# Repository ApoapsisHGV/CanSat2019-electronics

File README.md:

# CanSat-Electronics
Circuit and PCB design files related to our 2019 CanSat competition

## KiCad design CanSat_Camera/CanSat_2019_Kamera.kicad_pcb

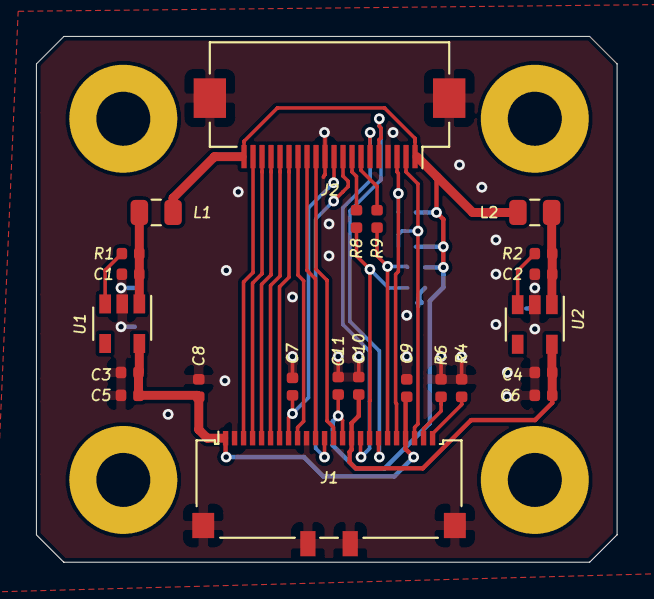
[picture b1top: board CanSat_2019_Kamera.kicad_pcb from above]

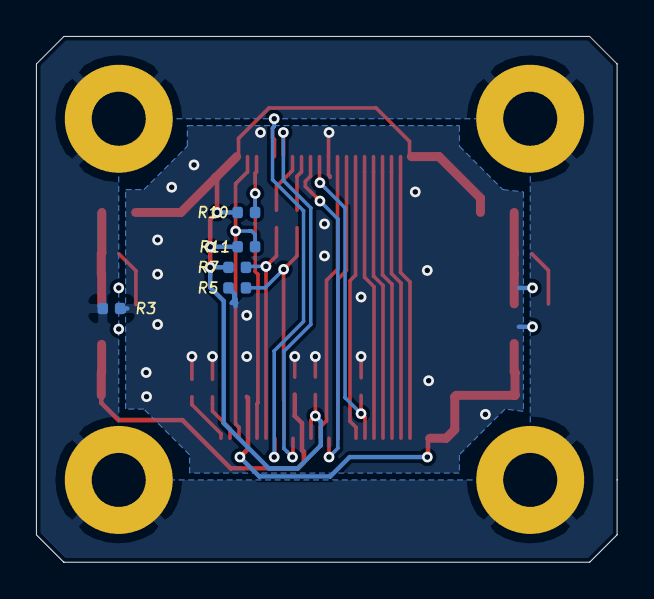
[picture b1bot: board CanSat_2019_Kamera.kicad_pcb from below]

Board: 2 copper layers, 32.3 x 29.2 mm, 32 parts (5 on the bottom side), 29 nets.

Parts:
C1, C2, C3, C4: 4.7u; C_0402_1005Metric
C5, C6, C8, C9, C10, C11: 100n; C_0402_1005Metric
C7: 15 pF; C_0402_1005Metric
H1, H2, H3, H4: MountingHole_Pad; MountingHole_3mm_Pad
J1: OV5640 24 Pin 0.5 mm; Molex_502244-2430_1x24-1MP_P0.5mm_Horizontal
J2: Camera Out 20 Pin 0.5 mm; Hirose_FH12-20S-0.5SH_1x20-1MP_P0.50mm_Horizontal
L1, L2: 3.3uH; L_0805_2012Metric
R1, R2, R4: 10k; R_0402_1005Metric
R3, R5, R6, R8, R9: 0; R_0402_1005Metric
R7, R10, R11: 4.7k; R_0402_1005Metric
U1: TLV75528PDBV; SOT-23-5
U2: TLV75518PDBV; SOT-23-5

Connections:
+1V8: C4.1, C6.1, C10.1, J1.15, U2.5
+2V8: C3.1, C5.1, C8.1, C9.1, J1.1, J1.21, U1.5
+3V3: C11.1, J1.14, J2.1, J2.20, L1.1, L2.1, R7.1, R10.1, R11.1
/D2: J1.6, J2.16
/D3: J1.4, J2.18
/D4: J1.3, J2.19
/D5: J1.5, J2.17
/D6: J1.7, J2.15
/D7: J1.9, J2.14
/D8: J1.11, J2.13
/D9: J1.13, J2.12
/H_REF: J1.16, J2.6
/P_CLK: C7.1, J1.8, J2.10
/P_DWN: J1.17, R5.1, R8.1
/RST: J1.19, R7.2, R9.1
/S_CLK: J1.20, J2.3, R10.2
/S_DAT: J1.22, J2.2, R11.2
/V_SYNC: J1.18, J2.5
/X_CLK: J1.12, J2.9
AGND: J1.23, R6.2
GND: C1.2, C2.2, C3.2, C4.2, C5.2, C6.2, C7.2, C8.2, C9.2, C10.2, C11.2, J1.2, J1.10, J1.MP, J2.4, J2.11, J2.MP, R3.2, R4.2, R5.2, R6.1, U1.2, U2.2
unnamed: C1.1, L1.2, R1.2, U1.1
unnamed: C2.1, L2.2, R2.2, U2.1
unnamed: H1.1, H2.1, H3.1, H4.1, R3.1
unnamed: J1.24, R4.1
unnamed: J2.7, R9.2
unnamed: J2.8, R8.2
unnamed: R1.1, U1.3
unnamed: R2.1, U2.3

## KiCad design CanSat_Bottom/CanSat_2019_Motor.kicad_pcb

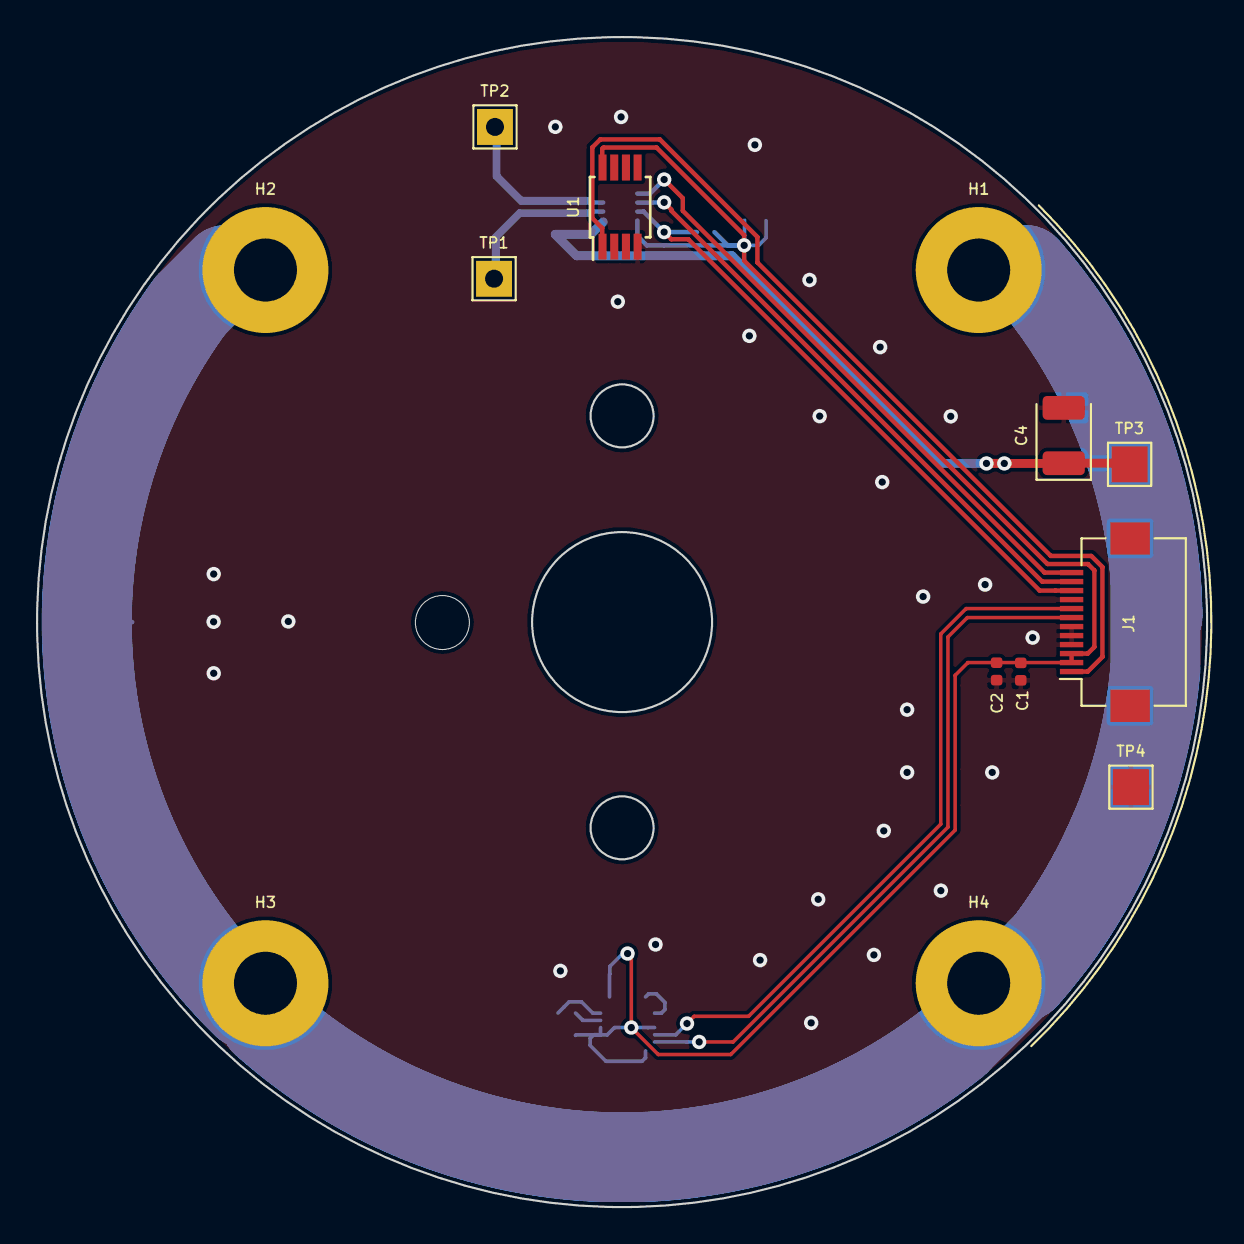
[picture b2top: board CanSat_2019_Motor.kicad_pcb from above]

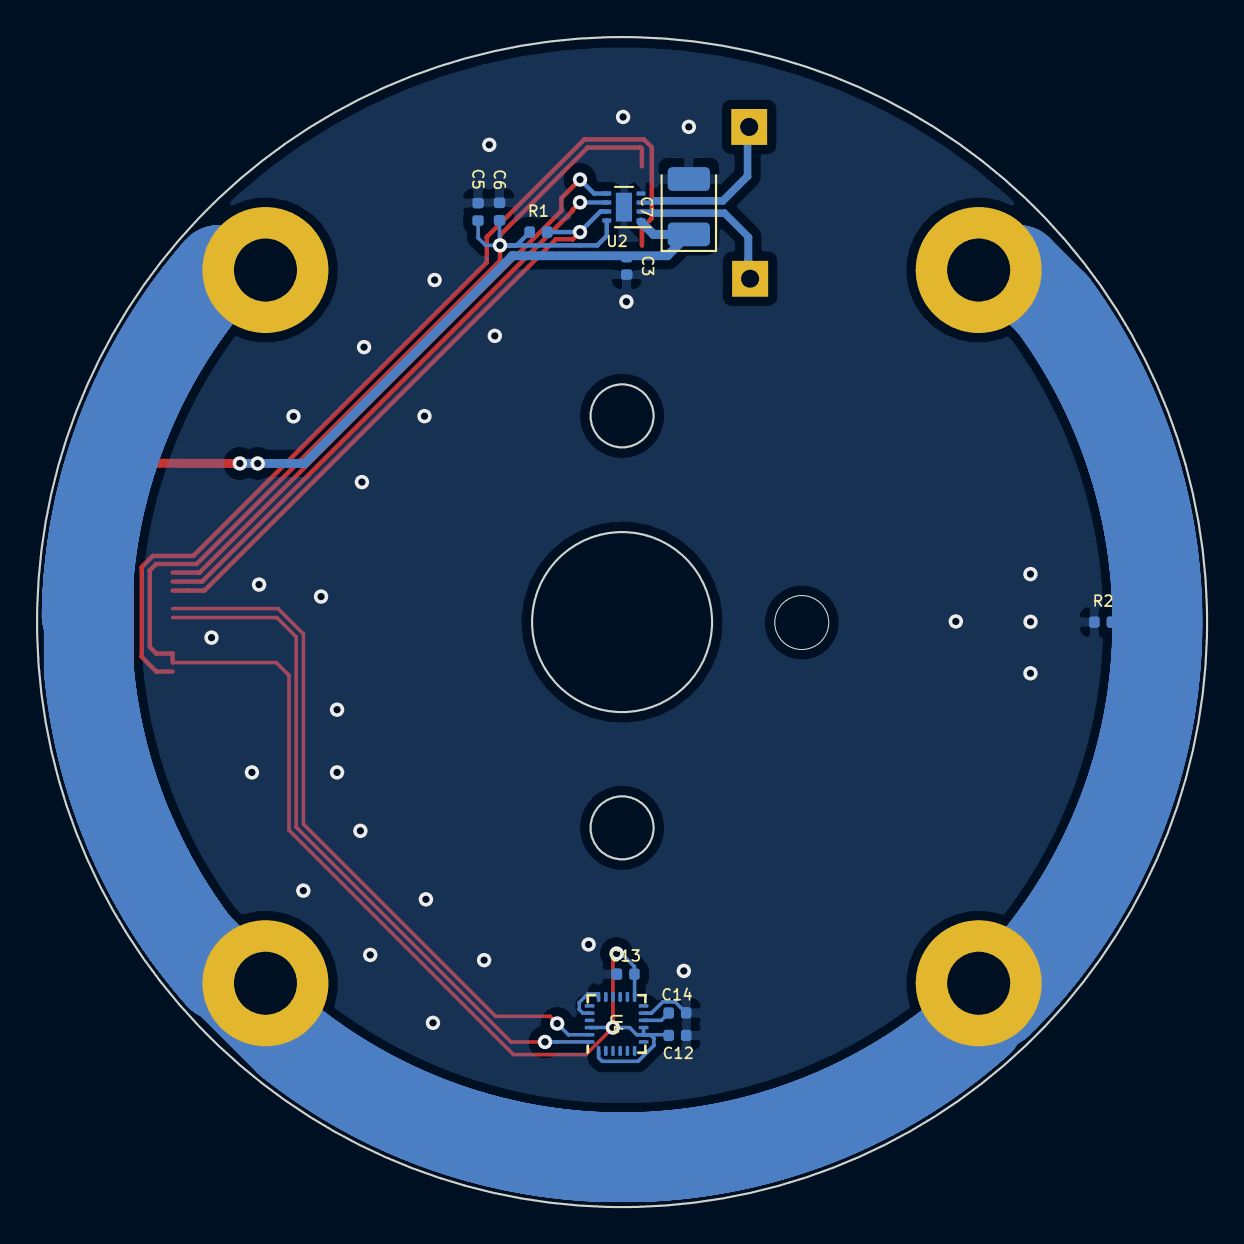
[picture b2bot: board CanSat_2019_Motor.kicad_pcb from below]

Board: 2 copper layers, 65.0 x 65.0 mm, 24 parts (11 on the bottom side), 13 nets.

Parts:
C1: 10u; C_0402_1005Metric
C2, C3, C5, C6, C12, C13, C14: 100n; C_0402_1005Metric
C4, C7: 22uF; CP_EIA-3528-12_Kemet-T
H1, H2, H3, H4: MountingHole_Pad; MountingHole_3.5mm_Pad
J1: Conn_01x12_Female; Hirose_FH12-12S-0.5SH_1x12-1MP_P0.50mm_Horizontal
R1: 10k; R_0402_1005Metric
R2: 1M; R_0402_1005Metric
TP1: Motor+; TestPoint_THTPad_2.0x2.0mm_Drill1.0mm
TP2: Motor-; TestPoint_THTPad_2.0x2.0mm_Drill1.0mm
TP3: VCC; TestPoint_Pad_2.0x2.0mm
TP4: GND; TestPoint_Pad_2.0x2.0mm
U1: DS18B20U; MSOP-8_3x3mm_P0.65mm
U2: DRV8838; WSON-8-1EP_2x2mm_P0.5mm_EP0.9x1.6mm
U4: MPU-9250; InvenSense_QFN-24_3x3mm_P0.4mm

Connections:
+3V3: C1.1, C2.1, C5.1, C6.1, C12.1, C13.1, J1.2, J1.3, R1.1, U1.8, U2.8, U4.1, U4.8, U4.9, U4.13, U4.22
/Motor_Enable: J1.12, U2.5
/Motor_Phase: J1.11, U2.6
/Motor_Sleep: J1.10, R1.2, U2.7
/OneWire: J1.1, U1.1
/SCL: J1.8, U4.23
/SDA: J1.7, U4.24
GND: C1.2, C2.2, C3.2, C4.2, C5.2, C6.2, C7.2, C12.2, C13.2, C14.2, J1.4, J1.5, J1.6, J1.9, R2.1, TP4.1, U1.4, U2.4, U2.9, U4.11, U4.18, U4.20
unnamed: C14.1, U4.10
unnamed: H1.1, H2.1, H3.1, H4.1, R2.2
unnamed: TP1.1, U2.2
unnamed: TP2.1, U2.3
VCC: C3.1, C4.1, C7.1, TP3.1, U2.1

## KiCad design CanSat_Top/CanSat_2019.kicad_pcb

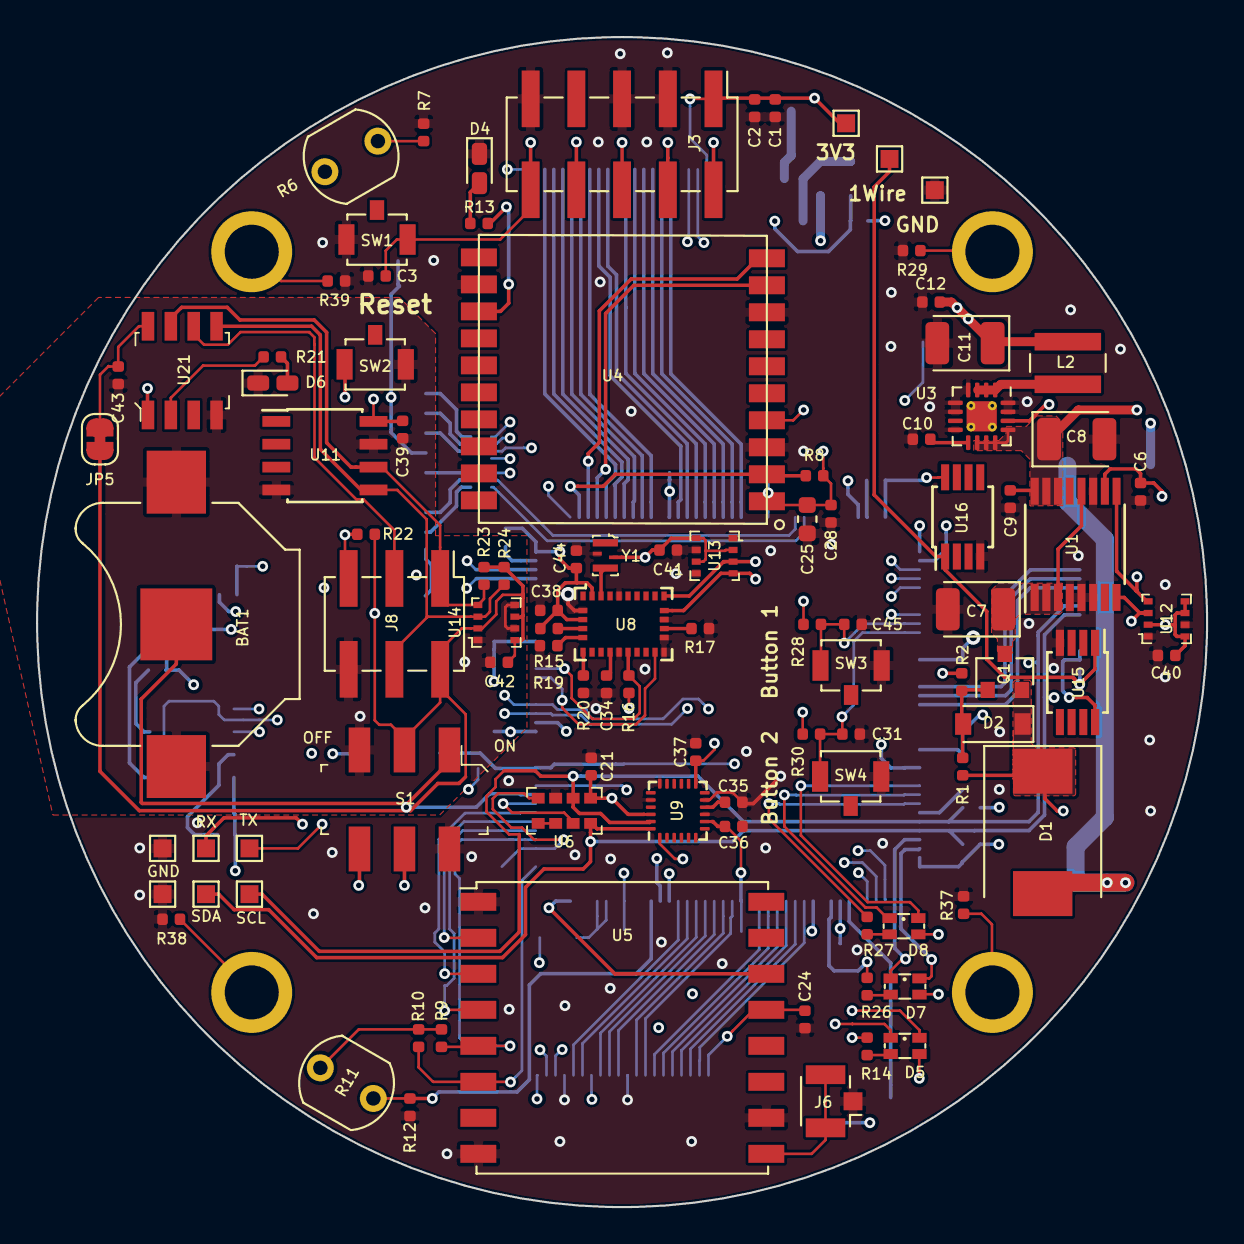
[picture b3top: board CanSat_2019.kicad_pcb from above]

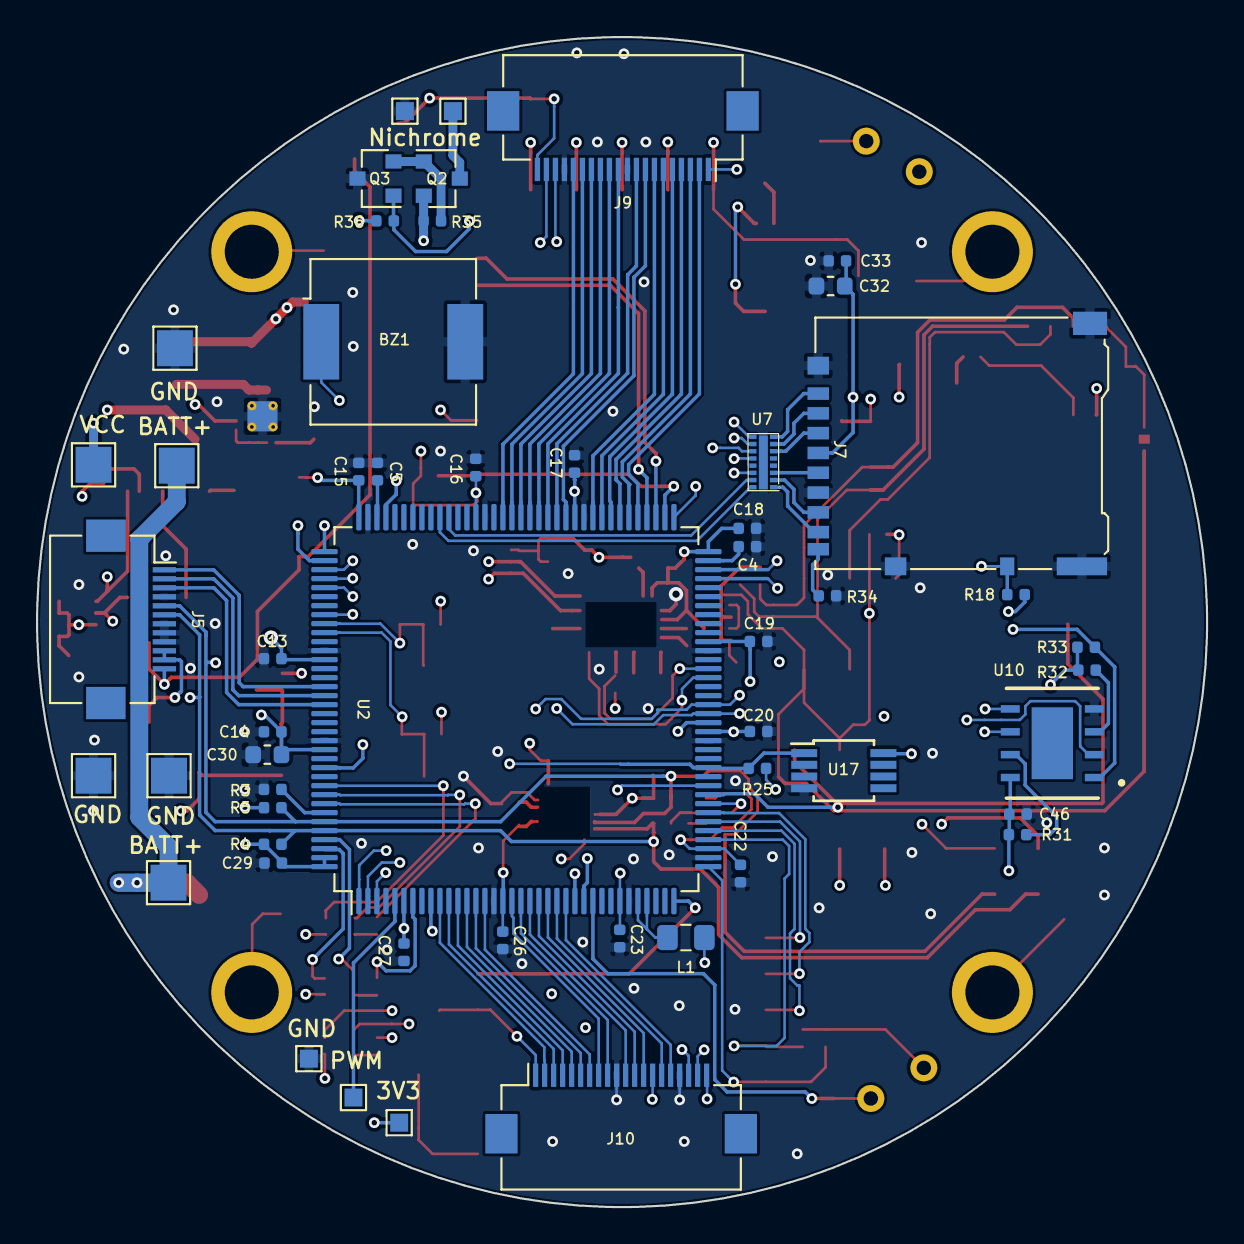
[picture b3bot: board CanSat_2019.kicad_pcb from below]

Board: 6 copper layers, 65.0 x 65.0 mm, 155 parts (53 on the bottom side), 132 nets.

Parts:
BAT1: BS-7; BatteryHolder_Keystone_3000_1x12mm
BZ1: Buzzer; Buzzer_CUI_CPT-9019S-SMT
C1, C3, C6, C9, C12, C13, C14, C15, C16, C17, C18, C19, C20, C21, C22, C23, C24, C26, C27, C29, C31, C34, C35, C36, C37, C38, C39, C40, C41, C42, C43, C44, C45, C46: 100nF; C_0402_1005Metric
C2: 1uF; C_0402_1005Metric
C4, C5: 2.2uF; C_0402_1005Metric
C7: 10uF; CP_EIA-3528-12_Kemet-T
C8, C11: 22uF; CP_EIA-3528-12_Kemet-T
C10: 3.3n; C_0402_1005Metric
C25: 1u; C_0603_1608Metric
C28, C33: 100n; C_0402_1005Metric
C30: 4.7u; C_0603_1608Metric
C32: 10u; C_0603_1608Metric
D1: D_Schottky; D_SMC
D2: 10V; D_SOD-123
D4, D6: LED; LED_0603_1608Metric_Castellated
D5, D7, D8: RGBA; LED_2.4mmx1.45mm_RGBA
H1, H2, H3, H4: MountingHole_Pad; MountingHole_3mm_Pad
J3: Conn_SWD_10; PinHeader_2x05_P2.54mm_Vertical_SMD
J5: 505110-1292 FFC; Hirose_FH12-12S-0.5SH_1x12-1MP_P0.50mm_Horizontal
J6: 0734120114; U.FL_Hirose_U.FL-R-SMT-1_Vertical
J7: Micro_SD_Card_Det_Hirose_DM3AT; microSD_HC_Hirose_DM3AT-SF-PEJM5
J8: AVR-ISP-6; PinHeader_2x03_P2.54mm_Vertical_SMD
J9: 20Pin FFC; Hirose_FH12-20S-0.5SH_1x20-1MP_P0.50mm_Horizontal
J10: 20 Pin FFC; Hirose_FH12-20S-0.5SH_1x20-1MP_P0.50mm_Horizontal
JP5: Power_Select; SolderJumper-2_P1.3mm_Bridged_RoundedPad1.0x1.5mm
L1: 1uH; L_0805_2012Metric_Pad1.15x1.40mm_HandSolder
L2: 2.2uH; L_Wuerth_MAPI-4020
Q1, Q2, Q3: SSM3J338R; SOT-23
R1, R18: 100k; R_0402_1005Metric
R2, R3, R8, R9, R10, R15, R16, R17, R19, R20, R22, R31, R32, R33, R35, R36: 10k; R_0402_1005Metric
R4, R5, R23, R24, R25: 4.7k; R_0402_1005Metric
R6, R11: GL5528; R_LDR_5.1x4.3mm_P3.4mm_Vertical
R7, R12, R28, R29, R30, R37, R38, R39: 1M; R_0402_1005Metric
R13, R21: 270; R_0402_1005Metric
R14, R26, R27: 50R; R_0402_1005Metric
R34: 1k; R_0402_1005Metric
S1: JS202011SCQN; Switch_Slide_JS202011SCQN
SW1, SW2, SW3, SW4: SW_Push; SW_SPST_B3U-1100P
TP1: ST_TX; TestPoint_Pad_1.0x1.0mm
TP2: ST_RX; TestPoint_Pad_1.0x1.0mm
TP3: Servo 3V3; TestPoint_Pad_1.0x1.0mm
TP4: Servo Control; TestPoint_Pad_1.0x1.0mm
TP5: Batt1+; TestPoint_Pad_2.0x2.0mm
TP6: Batt1-; TestPoint_Pad_2.0x2.0mm
TP7: Batt2+; TestPoint_Pad_2.0x2.0mm
TP8: Batt2-; TestPoint_Pad_2.0x2.0mm
TP9: Bottom+; TestPoint_Pad_2.0x2.0mm
TP10: Bottom-; TestPoint_Pad_2.0x2.0mm
TP11: Nichrome +; TestPoint_Pad_1.0x1.0mm
TP12: Servo GND; TestPoint_Pad_1.0x1.0mm
TP13: Nichrome -; TestPoint_Pad_1.0x1.0mm
TP14: SCl; TestPoint_Pad_1.0x1.0mm
TP15: SDA; TestPoint_Pad_1.0x1.0mm
TP16, TP17: GND; TestPoint_Pad_1.0x1.0mm
TP18: DS18B20 3V3; TestPoint_Pad_1.0x1.0mm
TP19: OneWire; TestPoint_Pad_1.0x1.0mm
TP20: DS18B20 GND; TestPoint_Pad_1.0x1.0mm
U1: INA260; TSSOP-16_4.4x5mm_P0.65mm
U2: STM32H743ZITx; LQFP-144_20x20mm_P0.5mm
U3: TPS62132; VQFN-16-1EP_3x3mm_P0.5mm_EP1.68x1.68mm_ThermalVias
U4: PA6H; PA6H_GPS
U5: RFM69HCW; HOPERF_RFM9XW_SMD
U6: APDS-9960; Ambient_Prox_APDS-9960
U7: CM1624; UDFN-16_3x1.5mm_P0.4
U8: BNO055; LGA-28_5.2x3.8mm_BNO0055
U9: MPU-9250; InvenSense_QFN-24_3x3mm_P0.4mm
U10: W25M02GV; SON127P600X500X80-9N
U11: M24M02-DRMN6TB; SOIC-8_3.9x4.9mm_P1.27mm
U12, U13, U14: BME280; Pressure_Sensor_LGA-8_2.5x2.5mm_BME280
U15, U16, U17: DS18B20U; MSOP-8_3x3mm_P0.65mm
U21: ATTINY85-20SU; SOIC-8_W5.3mm
Y1: SIT1533AI-H4-DCC-32_768E; Oscillator_MEMS_SIT1533AI-H4-DCC-32.768E

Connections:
+3V3: C1.1, C2.1, C6.1, C11.1, C12.1, C13.1, C14.1, C15.1, C16.1, C17.1, C18.1, C19.1, C20.1, C21.1, C22.1, C23.1, C24.1, C25.1, C26.1, C27.1, C28.1, C29.1, C30.1, C32.1, C33.1, C36.1, C37.1, C38.1, C40.1, C41.1, C44.1, C46.1, D5.4, D7.4, D8.4, J3.1, J5.10, J5.11, J7.4, J9.1, J9.20, J10.1, J10.20, L1.1, L2.2, R4.1, R5.1, R6.1, R8.1, R9.1, R10.1, R11.1, R15.1, R16.1, R18.1, R25.1, R28.2, R30.2, R31.1, R32.1, R33.1, R36.1, TP3.1, TP18.1, U1.10, U2.6, U2.17, U2.30, U2.39, U2.52, U2.62, U2.72, U2.84, U2.95, U2.108, U2.121, U2.131, U2.143, U2.144, U3.14, U4.1, U4.4, U5.13, U6.5, U6.8, U7.12, U8.3, U8.28, U9.1, U9.8, U9.13, U9.22, U10.8, U12.2, U12.5, U12.6, U12.8, U13.2, U13.6, U13.8, U15.8, U16.8, U17.8, Y1.4
+BATT: C39.1, C42.1, J8.2, JP5.1, R22.1, R23.1, R24.1, S1.2, U11.8, U14.2, U14.6, U14.8
/1PPS: R13.1, U4.13
/APDS_Int: U2.44, U6.2
/BNO_Int: U2.58, U8.14
/BNO_RST: R16.2, U2.59, U8.11
/Blue_1: D5.3, U2.3
/Blue_2: D7.3, U2.142
/Blue_3: D8.3, U2.135
/Boot0: R3.1, U2.138
/Button_1: C45.1, R28.1, SW3.1, U2.117
/Button_2: C31.1, R30.1, SW4.1, U2.118
/Buzzer: BZ1.1, U2.46
/CardDetect: J7.10, R18.2, U2.73
/D2-1: J10.5, U2.13
/D2-2: J9.5, U2.80
/D3-1: J10.3, U2.11
/D3-2: J9.3, U2.78
/D4-1: J10.2, U2.10
/D4-2: J9.2, U2.77
/D5-1: J10.4, U2.12
/D5-2: J9.4, U2.79
/D6-1: J10.6, U2.14
/D6-2: J9.6, U2.81
/D7-1: J10.7, U2.15
/D7-2: J9.7, U2.82
/D8-1: J10.8, U2.18
/D8-2: J9.8, U2.85
/D9-1: J10.9, U2.19
/D9-2: J9.9, U2.86
/GPS_RST: R8.2, U2.74, U4.2
/GPS_RX: U2.75, U4.10
/GPS_TX: U2.76, U4.9
/Green_1: D5.2, U2.2
/Green_2: D7.2, U2.141
/Green_3: D8.2, U2.136
/HREF-1: J10.15, U2.23
/HREF-2: J9.15, U2.91
/Licht_L: R6.2, R7.1, U2.26
/Licht_R: R11.2, R12.1, U2.27
/MISO: U2.42, U5.2, U10.2
/MOSI: U2.43, U5.3, U10.5
/Motor_Enable: J5.1, U2.124
/Motor_Phase: J5.2, U2.125
/Motor_Sleep: J5.3, U2.126
/NRST: C3.1, J3.10, SW1.1, U2.25
/OneWire: J5.12, R25.2, TP19.1, U2.48, U15.1, U16.1, U17.1
/PCLK-1: J10.11, U2.20
/PCLK-2: J9.11, U2.87
/PDWN-1: J10.13, U2.22
/PDWN-2: J9.13, U2.89
/Pyro: Q3.1, R36.2, U2.53
/RFM_CS: R9.2, U2.40, U5.5
/RFM_DI0: U2.36, U5.14
/RFM_RST: R10.2, U2.37, U5.6
/RST-1: J10.14, U2.9
/RST-2: J9.14, U2.90
/Red_1: R14.1, U2.1
/Red_2: R26.1, U2.7
/Red_3: R27.1, U2.137
/SCK: U2.41, U5.4, U10.6
/SCL: J5.5, R5.2, TP14.1, U1.9, U2.139, U6.7, U8.19, U9.23, U12.4, U13.4
/SCLK_Camera: J9.18, J10.18, U2.54
/SDA: J5.6, R4.2, TP15.1, U1.8, U2.140, U6.1, U8.20, U9.24, U12.3, U13.3
/SDAT_Camera: J9.19, J10.19, U2.55
/SD_CLK: U2.113, U7.14
/SD_CMD: U2.116, U7.11
/SD_DAT0: U2.98, U7.15
/SD_DAT1: U2.99, U7.16
/SD_DAT2: U2.111, U7.9
/SD_DAT3: U2.112, U7.10
/Serial_RX: TP2.1, U2.70
/Serial_TX: TP1.1, U2.69
/Servo: TP4.1, U2.5
/Storage_CS: R33.2, U2.45, U10.1
/TCK: J3.4, U2.109
/TDI: J3.8, U2.110
/TDO: J3.6, U2.133
/TMS: J3.2, U2.105
/Tiny_MISO: J8.3, U21.6
/Tiny_RST: J8.5, R22.2, SW2.2, U21.1
/Tiny_SCL: J8.1, R23.2, U11.6, U14.4, U21.7
/Tiny_SDA: J8.4, R24.2, U11.5, U14.3, U21.5
/VSYNC-1: J10.16, U2.24
/VSYNC-2: J9.16, U2.92
/XCLK-1: J10.12, U2.21
/XCLK-2: J9.12, U2.88
GND: BZ1.2, C1.2, C2.2, C3.2, C4.2, C5.2, C6.2, C7.2, C8.2, C9.2, C10.2, C11.2, C12.2, C13.2, C14.2, C15.2, C16.2, C17.2, C18.2, C19.2, C20.2, C21.2, C22.2, C23.2, C24.2, C25.2, C26.2, C27.2, C28.2, C29.2, C30.2, C31.2, C32.2, C33.2, C34.2, C35.2, C36.2, C37.2, C38.2, C40.2, C41.2, C44.2, C45.2, C46.2, D4.1, J3.3, J3.5, J3.9, J5.4, J5.7, J5.8, J5.9, J6.1, J7.6, J7.11, J9.10, J9.17, J10.10, J10.17, Q3.3, R3.2, R7.2, R12.2, R17.2, R19.2, R20.2, R29.1, R34.2, R37.1, R38.1, R39.1, S1.4, SW1.2, SW3.2, SW4.2, TP6.1, TP8.1, TP10.1, TP12.1, TP13.1, TP16.1, TP17.1, TP20.1, U1.4, U1.5, U1.6, U1.11, U2.16, U2.31, U2.38, U2.51, U2.61, U2.83, U2.94, U2.107, U2.120, U2.130, U3.4, U3.5, U3.6, U3.8, U3.15, U3.16, U3.17, U4.3, U4.8, U4.12, U4.19, U5.1, U5.8, U5.10, U6.6, U7.17, U8.2, U8.10, U8.15, U8.16, U8.18, U8.25, U9.9, U9.11, U9.18, U9.20, U10.4, U12.1, U12.7, U13.1, U13.5, U13.7, U15.4, U16.4, U17.4, Y1.2
GNDS: BAT1.1, C39.2, C42.2, C43.2, D6.1, J8.6, S1.3, SW2.1, U11.4, U11.7, U14.1, U14.5, U14.7, U21.4
unnamed: BAT1.2, S1.1
unnamed: C4.1, U2.71
unnamed: C5.1, U2.106
unnamed: C7.1, Q1.3, U1.1, U1.2, U1.3, U1.12
unnamed: C10.1, U3.9
unnamed: C34.1, U8.9
unnamed: C35.1, U9.10
unnamed: C43.1, JP5.2, U21.8
unnamed: D1.2, TP5.1, TP7.1
unnamed: D2.2, Q1.1, R1.2, R2.1
unnamed: D4.2, R13.2
unnamed: D5.1, R14.2
unnamed: D6.2, R21.2
unnamed: D7.1, R26.2
unnamed: D8.1, R27.2
unnamed: H1.1, R37.2
unnamed: H2.1, R38.2
unnamed: H3.1, R39.2
unnamed: H4.1, R29.2
unnamed: J6.2, U5.9
unnamed: J7.1, U7.8
unnamed: J7.2, U7.7
unnamed: J7.3, U7.6
unnamed: J7.5, U7.3
unnamed: J7.7, U7.2
unnamed: J7.8, U7.1
unnamed: J7.9, R34.1
unnamed: L2.1, U3.1, U3.2, U3.3
unnamed: Q2.1, Q3.2, R35.2
unnamed: Q2.3, TP11.1
unnamed: R2.2, S1.5
unnamed: R15.2, U8.4
unnamed: R17.1, U8.17
unnamed: R19.1, U8.5
unnamed: R20.1, U8.6
unnamed: R21.1, U21.2
unnamed: R31.2, U10.7
unnamed: R32.2, U10.3
unnamed: U6.3, U6.4
unnamed: U8.27, Y1.3
VCC: C8.1, C9.1, Q2.2, R35.1, TP9.1, U1.14, U1.15, U1.16, U3.10, U3.11, U3.12, U3.13
VDDA: L1.2, U2.32, U2.33
VPP: D1.1, D2.1, Q1.2, R1.1, S1.6

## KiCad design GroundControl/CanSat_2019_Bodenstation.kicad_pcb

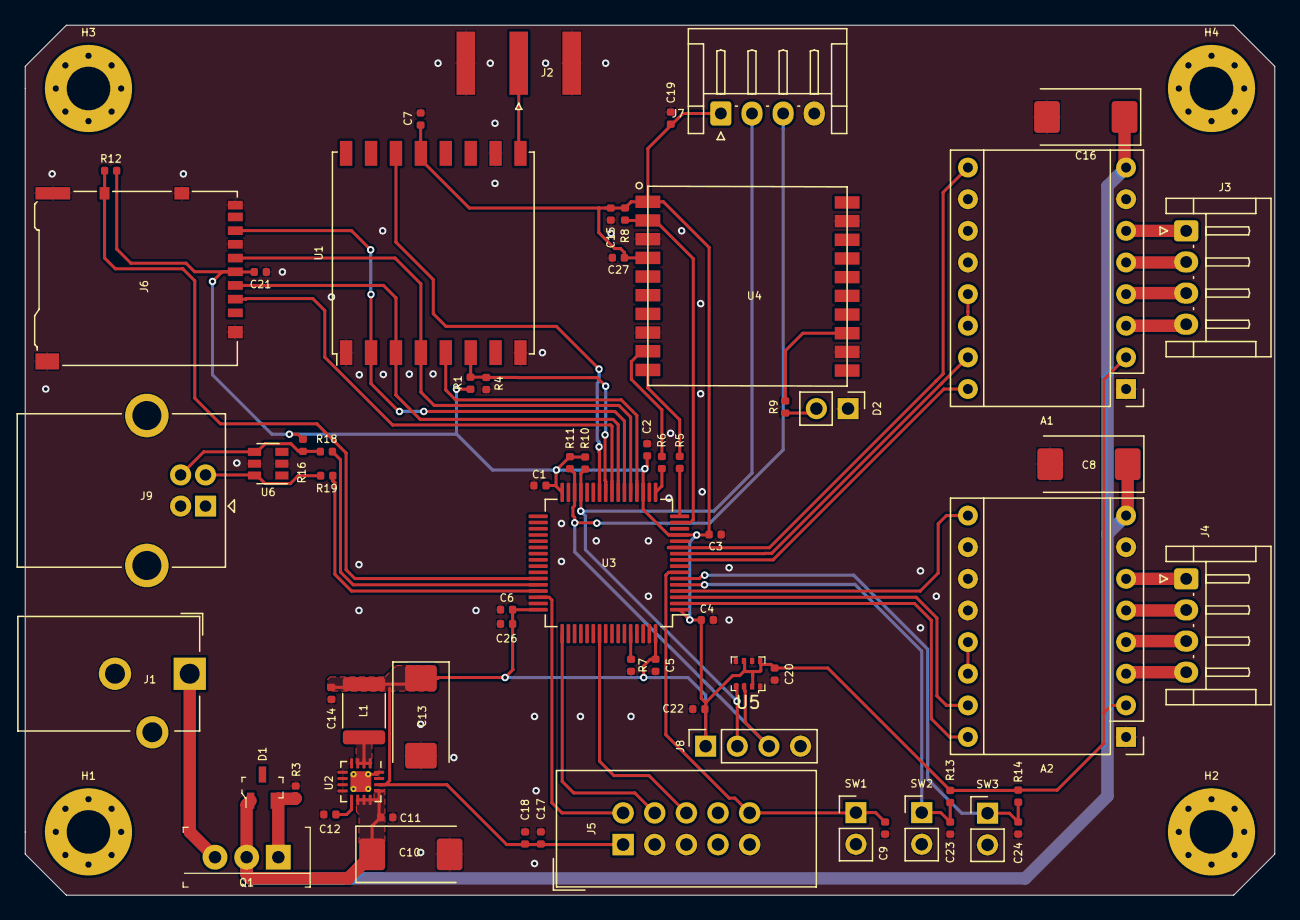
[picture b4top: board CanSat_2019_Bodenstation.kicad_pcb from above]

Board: 2 copper layers, 100.3 x 69.8 mm, 70 parts (0 on the bottom side), 52 nets.

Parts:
A1, A2: Pololu_A4988; Pololu_Breakout-16_15.2x20.3mm
C1, C2, C3, C4, C5, C6, C7, C9, C11, C14, C15, C18, C20, C21, C23, C24: 100n; C_0402_1005Metric
C8, C16: 100uF; CP_EIA-7343-15_Kemet-W
C10, C13: 22u; CP_EIA-7343-15_Kemet-W
C12: 3.3n; C_0402_1005Metric
C17: 1u; C_0402_1005Metric
C19, C22, C27: 10u; C_0402_1005Metric
C26: 4.7u; C_0402_1005Metric
D1: 10V; SOT-23-3
D2: Blue; PinHeader_1x02_P2.54mm_Vertical
H1, H2, H3, H4: MountingHole_3.5; MountingHole_3.5mm_Pad_Via
J1: Barrel_Jack_Switch; BarrelJack_CUI_PJ-102AH_Horizontal
J2: Conn_Coaxial; SMA_Amphenol_132289_EdgeMount
J3: Motor-XY; JST_EH_S4B-EH_1x04_P2.50mm_Horizontal
J4: Motor-Z; JST_EH_S4B-EH_1x04_P2.50mm_Horizontal
J5: Conn_SWD_10; IDC-Header_2x05_P2.54mm_Vertical
J6: Micro_SD_Card_Det_Hirose_DM3AT; microSD_HC_Hirose_DM3AT-SF-PEJM5
J7: Gyro; JST_EH_S4B-EH_1x04_P2.50mm_Horizontal
J8: Display; PinSocket_1x04_P2.54mm_Vertical
J9: USB_B; USB_B_OST_USB-B1HSxx_Horizontal
L1: 2.2u; L_1812_4532Metric
Q1: FQP27P06; TO-220-3
R1, R3, R4, R7, R8, R12: 10k; R_0402_1005Metric
R5, R6: 1k; R_0402_1005Metric
R9: 200; R_0402_1005Metric
R10, R11: 4k7; R_0402_1005Metric
R13, R14: 1M; R_0402_1005Metric
R16: 1.5k; R_0402_1005Metric
R18, R19: 20; R_0402_1005Metric
SW1, SW2, SW3: SW_Push; PinHeader_1x02_P2.54mm_Vertical
U1: RFM69HCW; HOPERF_RFM9XW_SMD
U2: TPS62132; VQFN-16-1EP_3x3mm_P0.5mm_EP1.68x1.68mm_ThermalVias
U3: STM32F103RBTx; LQFP-64_10x10mm_P0.5mm
U4: PA6H; PA6H_GPS
U5: BME280; Pressure_Sensor_LGA-8_2.5x2.5mm_BME280
U6: SN65220; SOT-23-6

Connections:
12V: A1.8, A2.8, C8.1, C10.1, C11.1, C16.1, D1.1, Q1.2, U2.10, U2.11, U2.12, U2.13
+3V3: A1.2, A2.2, C1.1, C2.1, C3.1, C4.1, C5.1, C6.1, C7.1, C13.1, C14.1, C15.1, C17.1, C18.1, C19.1, C20.1, C21.1, C22.1, C26.1, C27.1, J5.1, J6.4, J7.1, J8.1, L1.2, R1.1, R8.1, R10.1, R11.1, R12.1, R13.1, R14.1, R16.1, U1.13, U2.14, U3.1, U3.13, U3.19, U3.32, U3.48, U3.64, U4.1, U4.4, U5.2, U5.6, U5.8
/Button_1: C23.1, R13.2, SW2.1, U3.5
/Button_2: C24.1, R14.2, SW3.1, U3.6
/DM: R19.1, U3.45
/DP: R18.1, U3.44
/GPS_RST: R8.2, U3.15, U4.2
/MISO: J6.7, U1.2, U3.22
/MOSI: J6.3, U1.3, U3.23
/RFM_CS: U1.5, U3.20
/RFM_INT: U1.14, U3.26
/RFM_RST: R1.2, R4.1, U1.6, U3.25
/RST: C9.1, J5.10, SW1.1, U3.7
/RX: R6.1, U4.9
/SCK: J6.5, U1.4, U3.21
/SCL: J7.2, J8.2, R10.2, U3.29, U5.4
/SDA: J7.3, J8.3, R11.2, U3.30, U5.3
/SD_CD: J6.10, R12.2, U3.43
/SD_CS: J6.2, U3.24
/SWO: J5.6, U3.55
/TCK: J5.4, U3.49
/TMS: J5.2, U3.46
/TX: R5.1, U4.10
/XY_DiR: A1.16, U3.9
/XY_EN: A1.9, U3.11
/XY_STP: A1.15, U3.10
/Z_DiR: A2.16, U3.2
/Z_EN: A2.9, U3.4
/Z_STP: A2.15, U3.3
GND: A1.1, A1.7, A1.10, A1.11, A1.12, A2.1, A2.7, A2.10, A2.11, A2.12, C1.2, C2.2, C3.2, C4.2, C5.2, C6.2, C7.2, C8.2, C9.2, C10.2, C11.2, C12.2, C13.2, C14.2, C15.2, C16.2, C17.2, C18.2, C19.2, C20.2, C21.2, C22.2, C23.2, C24.2, C26.2, C27.2, D2.1, J1.2, J1.3, J2.2, J5.3, J5.5, J5.9, J6.6, J6.9, J6.11, J7.4, J8.4, J9.4, J9.5, R3.2, R4.2, R7.2, SW1.2, SW2.2, SW3.2, U1.1, U1.8, U1.10, U2.4, U2.5, U2.6, U2.7, U2.8, U2.15, U2.16, U2.17, U3.12, U3.18, U3.31, U3.47, U3.63, U4.3, U4.8, U4.12, U4.19, U5.1, U5.5, U5.7, U6.2, U6.5
unnamed: A1.3, J3.4
unnamed: A1.4, J3.3
unnamed: A1.5, J3.2
unnamed: A1.6, J3.1
unnamed: A1.13, A1.14
unnamed: A2.3, J4.4
unnamed: A2.4, J4.3
unnamed: A2.5, J4.2
unnamed: A2.6, J4.1
unnamed: A2.13, A2.14
unnamed: C12.1, U2.9
unnamed: D1.2, Q1.1, R3.1
unnamed: D2.2, R9.2
unnamed: J1.1, Q1.3
unnamed: J2.1, U1.9
unnamed: J9.2, R19.2, U6.6
unnamed: J9.3, R16.2, R18.2, U6.4
unnamed: L1.1, U2.1, U2.2, U2.3
unnamed: R5.2, U3.16
unnamed: R6.2, U3.17
unnamed: R7.1, U3.60
unnamed: R9.1, U4.13

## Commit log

2019-06-14 Initialization
2019-06-14 Update LICENSE
2019-06-14 Added OneWire Header and finished bottom PCB design
2019-06-15 Added vias
2019-06-15 updated files for production
